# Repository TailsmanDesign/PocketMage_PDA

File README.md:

# PocketMage PDA
PocketMage is available on Crowd Supply! Check it out [here](https://pocketmage.org/back)!

@Ashtf 2025

## [Project Summary]

  This project is a PDA powered by an ESP32-S3 running a custom OS written in C++ using PlatformIO. This project utilizes an E-Ink and OLED screen in tandem to mitigate the refresh rate restrictions of an E-Ink panel while retaining the aesthetics and benefits of using E-Ink. This project is a work in progress and currently amounts to a simple GUI for navigating between apps, a text (.txt) file editor, and a basic file manager. More applications are planned for the future and a list of TO-DOs can be found below.

  At this point, the plan for this project is to get the software and hardware to maturity and once a finished product is achieved, a few things will happen. First, the project files (Code, KiCad schematics, 3D files) will be open-sourced and free for anyone to access. Next, I will likely begin selling kits that allow people to purchase all the parts required to build a device for themselves if they don't want to source the parts themselves. Finally, the community will be encouraged to help develop the software for the device and hopefully push it even further than I could myself.

  I will try my best to keep this GitHub up to date with the development of the device.

## [Getting Started]

Start with the docs site:

- [PocketMage Docs](https://talismandesign.github.io/PocketMage_PDA/docs/)
- [Build Environments](https://talismandesign.github.io/PocketMage_PDA/docs/development/build-environments)
- [Command Manual](https://talismandesign.github.io/PocketMage_PDA/docs/command-manual)
- [FAQ](https://talismandesign.github.io/PocketMage_PDA/docs/faq)
- [Scripting](https://talismandesign.github.io/PocketMage_PDA/docs/scripting)
- [App API Reference](https://talismandesign.github.io/PocketMage_PDA/docs/reference/app-api)

To build or extend apps, start with [APP_TEMPLATE.cpp](./Code/PocketMageOS/src/APP_TEMPLATE.cpp) and the [App API Reference](https://talismandesign.github.io/PocketMage_PDA/docs/reference/app-api).
The app walkthrough video is still useful for a first pass:
[Developing For the PocketMage](https://www.youtube.com/watch?v=3Ytc-3-BbMM)

## [Hardware]

- ESP32-S3 WROOM1 with 16 MB flash and 8 MB RAM. WiFi and Bluetooth supported.
- 3.1" 320x240px 1-bit SPI E-Ink panel (GDEQ031T10) with integrated driver
- 256x32px 1-bit SPI OLED (SSD1326, ER-OLED018-1W) with integrated driver
- MicroSD card slot with support for up to 2 TB
- TCA8418 I2C keyboard matrix IC
- Piezo buzzer (simple tones)
- Power button
- 1200 mAh pouch-style LiPo battery with JST PH (2 mm) connector
- USB Type-C connector
- PCF8563T I2C RTC module
- Expansion port with the following breakouts:
  - +3.3V
  - GND
  - I2C SDA
  - I2C SCL
  - SPI MOSI
  - SPI SCK
  - SPI MISO
  - GPIO A
  - GPIO B
  - GPIO C
  - GPIO D / UART TX (changeable with a solder jumper, default TX)
  - GPIO E / UART RX (changeable with a solder jumper, default RX)

## [Software]

- Text editor app (TXT)
- FileWiz file-management app
- Calendar app
- USB file transfer app
- COMM mesh chat app
- Settings app
- Tasks app
- Journal app
- Dictionary app (Lexicon)
- App loader for OTA apps
- Terminal app (Wrench scripting)
- SSH
- Commands supported through the home menu:
  - `roll dN` (dice roll, N = number of sides)
  - set time and date
  - directly open files in TXT or FileWiz by typing the name
  - and more

## [Planned Features]

- Timers and alarms
- E-book reader
- WiFi notes/calendar sync (Google Docs/Calendar)
- LoRa/Meshtastic add-on module
- Battery expansion add-on module
- Custom abbreviations
- Bluetooth keyboard support

## License

All files are distributed under the Apache-2.0 license:

PocketMage PDA - A clamshell note-taking and productivity device using E-Ink and OLED.

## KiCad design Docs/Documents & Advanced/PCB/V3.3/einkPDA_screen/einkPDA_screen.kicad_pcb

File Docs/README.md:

# PocketMage Documentation

The documentation site for the PocketMage PDA project.

**Live docs: <https://talismandesign.github.io/PocketMage_PDA/docs/>**

---

## What's in here

The `docs/` folder contains all the source Markdown files that make up the documentation site. Sections include:

- **Getting Started** - what PocketMage is, setup, and first steps
- **PocketMageOS** - the operating system and runtime model
- **Guides** - making apps, native apps, OTA apps, and scripting
- **Reference** - app API, system state, and the PocketMage library
- **Commands** - keymaps and built-in command reference
- **Features** - what PocketMage can do today
- **FAQ** - common questions about the device, building, flashing, and troubleshooting
- **Tutorials** - SD card formatting and setup walkthroughs

The site is built using [docmd](https://github.com/mgks/docmd) and configured via `docmd.config.js`.

---

## Local development

You'll need Node.js 18+ installed.

Install dependencies:

```
npm install
```

Start the local dev server with live reload:

```
npm run dev
```

Build the static site to the `site/` output folder:

```
npm run build
```

Preview the built site locally:

```
npm run preview
```

---

## Contributing to the docs

Documentation source files live in `docs/` as standard Markdown with YAML front matter for title and description metadata.

To add or edit a page:

1. Create or modify a `.md` file in the appropriate subfolder under `docs/`.
2. If you are adding a new page, add it to the `navigation` array in `docmd.config.js` so it appears in the sidebar.
3. Run `npm run dev` to preview your changes locally before submitting.

Keep the writing short and direct. Use the overview pages to route readers into the exact guide or reference page they need.

---

## Project links

- Main repo: <https://github.com/TalismanDesign/PocketMage_PDA>
- Discord: <https://discord.gg/KSCapSf4XH>
- Website: <https://pocketmage.org/>

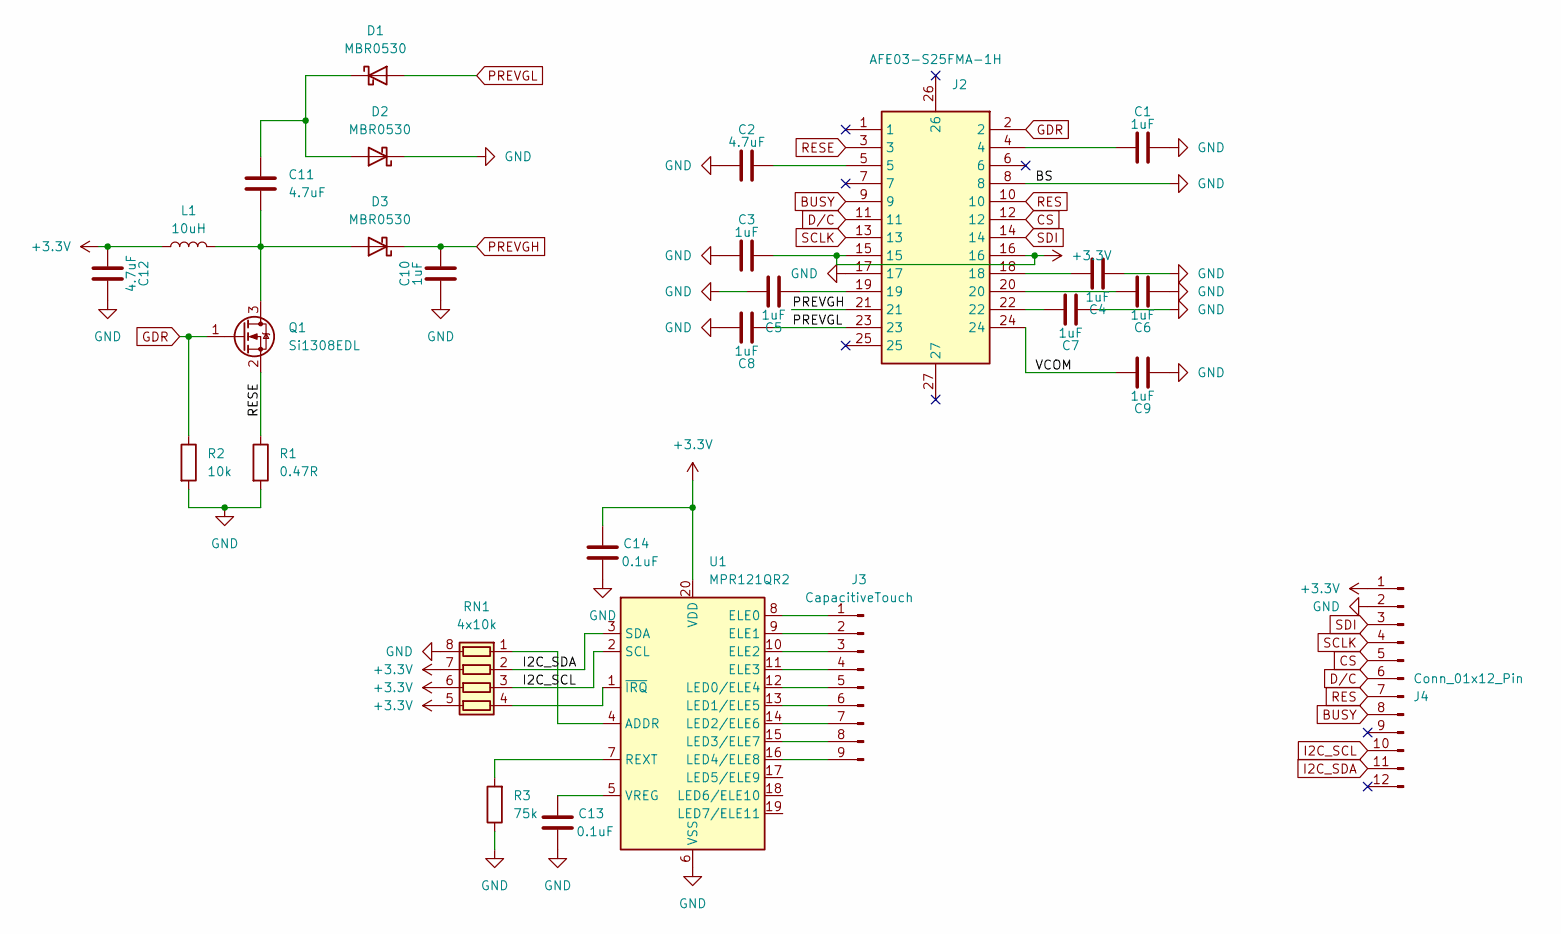
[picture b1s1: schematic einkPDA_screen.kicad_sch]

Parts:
C1, C3, C4, C5, C6, C7, C8, C9, C10: 1uF; C_0402_1005Metric; MPN C52923
C2, C12: 4.7uF; C_0402_1005Metric; MPN C23733
C11: 4.7uF; C_0805_2012Metric; MPN C1779
C13, C14: 0.1uF; C_0402_1005Metric; MPN C1525
D1, D2, D3: MBR0530; D_SOD-123; MPN C77336
J2: AFE03-S25FMA-1H; MPN C262544
J3: CapacitiveTouch; TouchSlider-9_50x10mm
J4: Conn_01x12_Pin; AFC01-S12FCA-00; MPN C262661
L1: 10uH; L_Cenker_CKCS5020; MPN C52281
Q1: Si1308EDL; SOT-323_SC-70; MPN C7603347
R1: 0.47R; R_0603_1608Metric; MPN C3013349
R2: 10k; R_0805_2012Metric; MPN C17414
R3: 75k; R_0603_1608Metric; MPN C23242
RN1: 4x10k; R_Array_Concave_4x0603; MPN C29718
U1: MPR121QR2; UQFN-20_3x3mm_P0.4mm; MPN C91322

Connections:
+3.3V: C3.2, C12.1, C14.1, J2.15, J2.16, J4.1, L1.1, RN1.5 (R4.2), RN1.6 (R3.2), RN1.7 (R2.2), U1.20 (VDD)
/VCOM: C9.2, J2.24
BUSY: J2.9, J4.8
CS: J2.12, J4.5
D/C: J2.11, J4.6
GDR: J2.2, Q1.1 (G), R2.1
GND: C1.2, C2.1, C3.1, C4.1, C5.2, C6.1, C7.1, C8.2, C9.1, C10.1, C12.2, C13.2, C14.2, D2.1 (K), J2.8, J2.17, J4.2, R1.2, R2.2, R3.1, RN1.8 (R1.2), U1.6 (VSS)
I2C_SCL: J4.10, RN1.3 (R3.1), U1.2 (SCL)
I2C_SDA: J4.11, RN1.2 (R2.1), U1.3 (SDA)
unnamed: C1.1, J2.4
unnamed: C2.2, J2.5
unnamed: C4.2, J2.18
unnamed: C5.1, J2.19
unnamed: C6.2, J2.20
unnamed: C7.2, J2.22
unnamed: C11.1, D1.1 (K), D2.2 (A)
unnamed: C11.2, D3.2 (A), L1.2, Q1.3 (D)
unnamed: J3.1, U1.8 (ELE0)
unnamed: J3.2, U1.9 (ELE1)
unnamed: J3.3, U1.10 (ELE2)
unnamed: J3.4, U1.11 (ELE3)
unnamed: J3.5, U1.12 (LED0/ELE4)
unnamed: J3.6, U1.13 (LED1/ELE5)
unnamed: J3.7, U1.14 (LED2/ELE6)
unnamed: J3.8, U1.15 (LED3/ELE7)
unnamed: J3.9, U1.16 (LED4/ELE8)
unnamed: RN1.1 (R1.1), U1.4 (ADDR)
unnamed: RN1.4 (R4.1), U1.1 (~IRQ)
unnamed: R3.2, U1.7 (REXT)
unnamed: C13.1, U1.5 (VREG)
PREVGH: C10.2, D3.1 (K), J2.21
PREVGL: C8.1, D1.2 (A), J2.23
RES: J2.10, J4.7
RESE: J2.3, Q1.2 (S), R1.1
SCLK: J2.13, J4.4
SDI: J2.14, J4.3

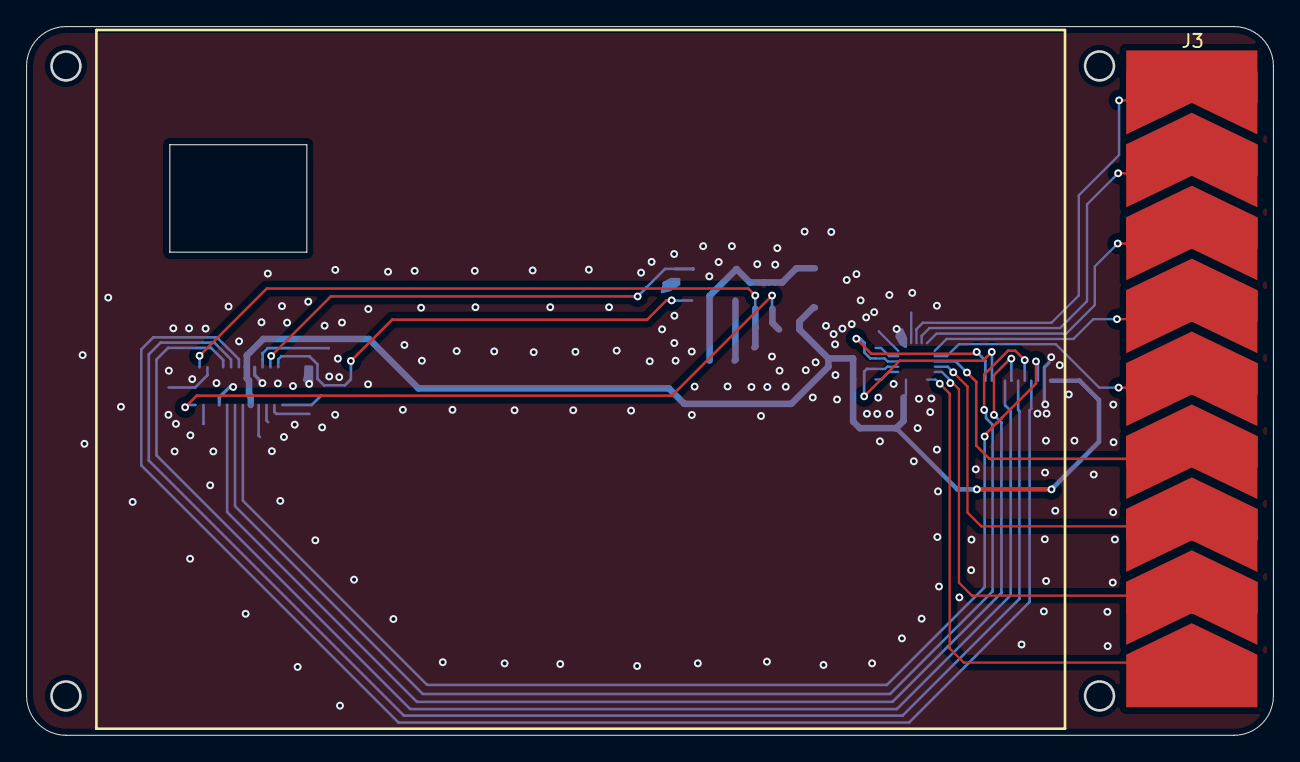
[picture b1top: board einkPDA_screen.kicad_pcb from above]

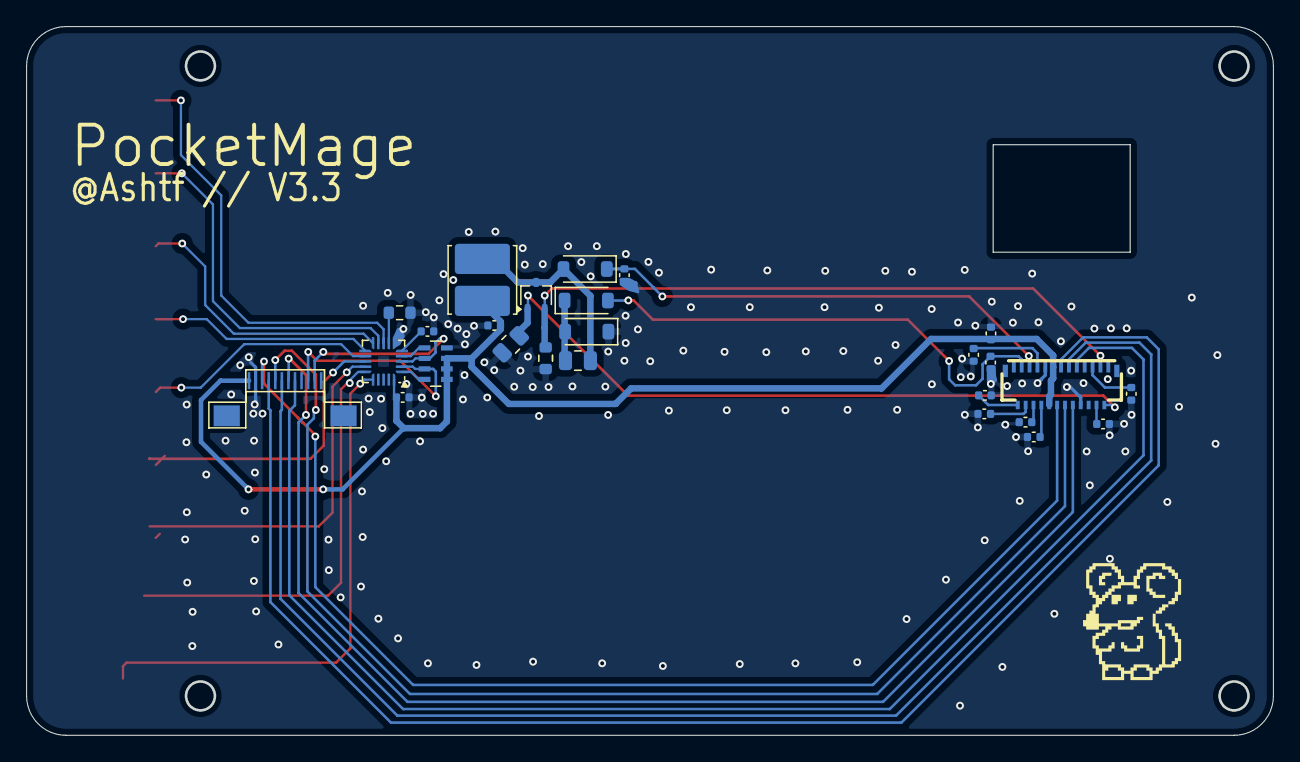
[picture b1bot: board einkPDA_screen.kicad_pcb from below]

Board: 2 copper layers, 95.0 x 54.0 mm, 27 parts (26 on the bottom side), 36 nets.

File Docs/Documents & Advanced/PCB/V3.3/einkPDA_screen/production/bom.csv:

Designator,Footprint,Quantity,Value,LCSC Part #
"C1, C10, C3, C4, C5, C6, C7, C8, C9",0402,9,1uF,C52923
C11,0805,1,4.7uF,C1779
"C12, C2",0402,2,4.7uF,C23733
"C13, C14",0402,2,0.1uF,C1525
"D1, D2, D3",D_SOD-123,3,MBR0530,C77336
J2,AFE03-S25FMA-1H,1,~,C262544
J3,TouchSlider-9_50x10mm,1,CapacitiveTouch,
J4,AFC01-S12FCA-00,1,Conn_01x12_Pin,C262661
L1,L_Cenker_CKCS5020,1,10uH,C52281
Q1,SOT-323_SC-70,1,Si1308EDL,C7603347
R1,0603,1,0.47R,C3013349
R2,0805,1,10k,C17414
R3,0603,1,75k,C23242
RN1,R_Array_Concave_4x0603,1,4x10k,C29718
U1,UQFN-20_3x3mm_P0.4mm,1,MPR121QR2,C91322

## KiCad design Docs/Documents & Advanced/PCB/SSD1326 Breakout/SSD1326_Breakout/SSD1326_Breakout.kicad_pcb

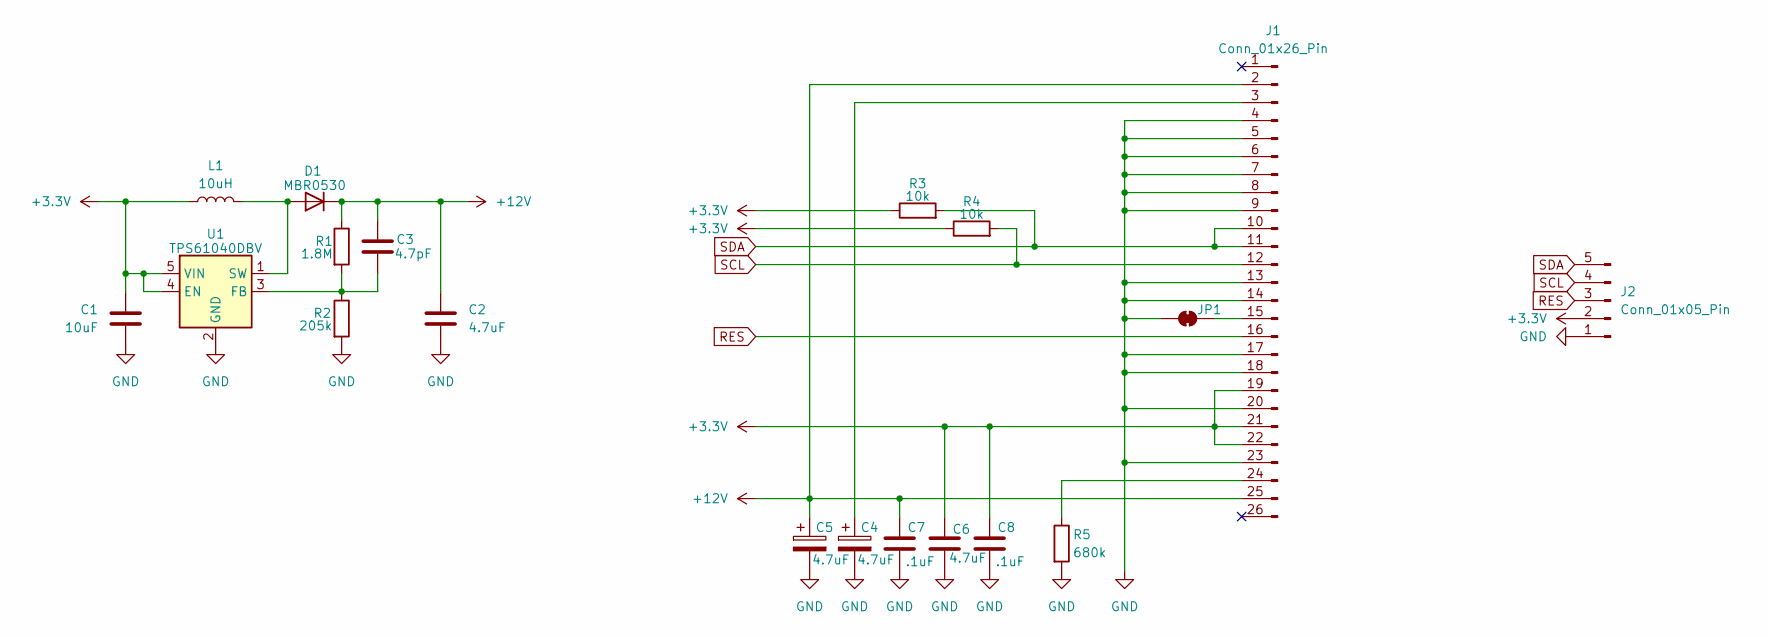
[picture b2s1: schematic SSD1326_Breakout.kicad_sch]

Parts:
C1: 10uF; C_0805_2012Metric; LCSC PART # C15850
C2, C6: 4.7uF; C_1206_3216Metric; LCSC PART # C29823
C3: 4.7pF; C_0603_1608Metric; LCSC PART # C1669
C4, C5: 4.7uF; CP_EIA-3216-18_Kemet-A; LCSC PART # C7189
C7, C8: .1uF; C_0805_2012Metric; LCSC PART # C28233
D1: MBR0530; D_SOD-123; LCSC PART # C77336
J1: Conn_01x26_Pin; FPC-SMD_AFC24-S26FIA [DUAL-SIDE]; LCSC PART # C262684
J2: Conn_01x05_Pin; PinHeader_1x05_P2.54mm_Vertical
JP1: SolderJumper_2_Bridged; SolderJumper-2_P1.3mm_Bridged_RoundedPad1.0x1.5mm
L1: 10uH; L_Chilisin_BMRx00060630; LCSC PART # C5189958
R1: 1.8M; R_0805_2012Metric; LCSC PART # C17399
R2: 205k; R_0805_2012Metric; LCSC PART # C218417
R3, R4: 10k; R_0805_2012Metric; LCSC PART # C17414
R5: 680k; R_0805_2012Metric; LCSC PART # C17797
U1: TPS61040DBV; SOT-23-5; LCSC PART # C7722

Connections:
+3.3V: C1.2, C6.1, C8.1, J1.19, J1.21, J1.22, J2.2, L1.1, R3.1, R4.1, U1.4 (EN), U1.5 (VIN)
+12V: C2.1, C3.2, C5.1, C7.1, D1.1 (K), J1.2, J1.25, R1.1
GND: C1.1, C2.2, C4.2, C5.2, C6.2, C7.2, C8.2, J1.4, J1.5, J1.6, J1.7, J1.8, J1.9, J1.13, J1.14, J1.17, J1.18, J1.20, J1.23, J2.1, JP1.1 (A), R2.2, R5.2, U1.2 (GND)
unnamed: D1.2 (A), L1.2, U1.1 (SW)
unnamed: C4.1, J1.3
unnamed: J1.15, JP1.2 (B)
unnamed: J1.24, R5.1
unnamed: C3.1, R1.2, R2.1, U1.3 (FB)
RES: J1.16, J2.3
SCL: J1.12, J2.4, R4.2
SDA: J1.10, J1.11, J2.5, R3.2

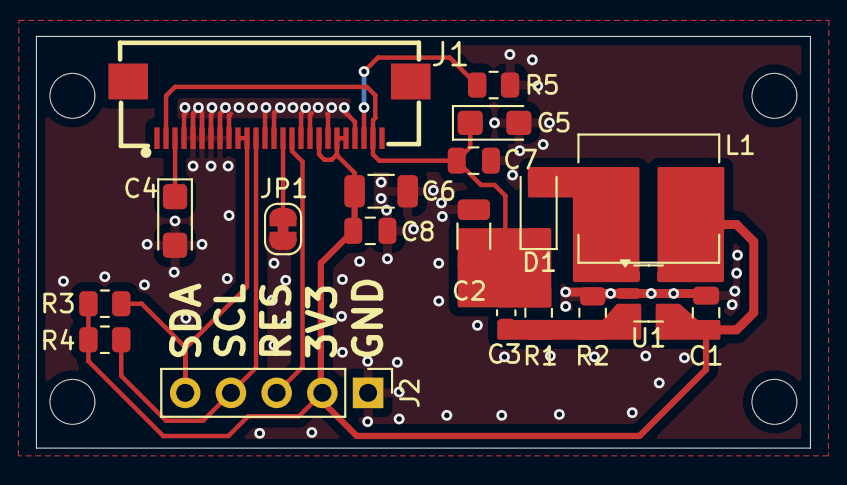
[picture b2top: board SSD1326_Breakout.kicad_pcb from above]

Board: 2 copper layers, 43.0 x 22.9 mm, 19 parts (0 on the bottom side), 11 nets.

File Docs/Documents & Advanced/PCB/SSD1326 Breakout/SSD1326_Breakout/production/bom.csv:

Designator,Footprint,Quantity,Value,LCSC Part #
C1,0805,1,10uF,
"C2, C6",1206,2,4.7uF,
C3,0603,1,4.7pF,
"C4, C5",CP_EIA-3216-18_Kemet-A,2,4.7uF,
"C7, C8",0805,2,.1uF,
D1,D_SOD-123,1,MBR0530,
J1,FPC-SMD_AFC24-S26FIA [DUAL-SIDE],1,Conn_01x26_Pin,
J2,PinHeader_1x05_P2.54mm_Vertical,1,Conn_01x05_Pin,
L1,L_Chilisin_BMRx00060630,1,10uH,
R1,0805,1,1.8M,
R2,0805,1,205k,
"R3, R4",0805,2,10k,
R5,0805,1,680k,
U1,SOT-23-5,1,TPS61040DBV,

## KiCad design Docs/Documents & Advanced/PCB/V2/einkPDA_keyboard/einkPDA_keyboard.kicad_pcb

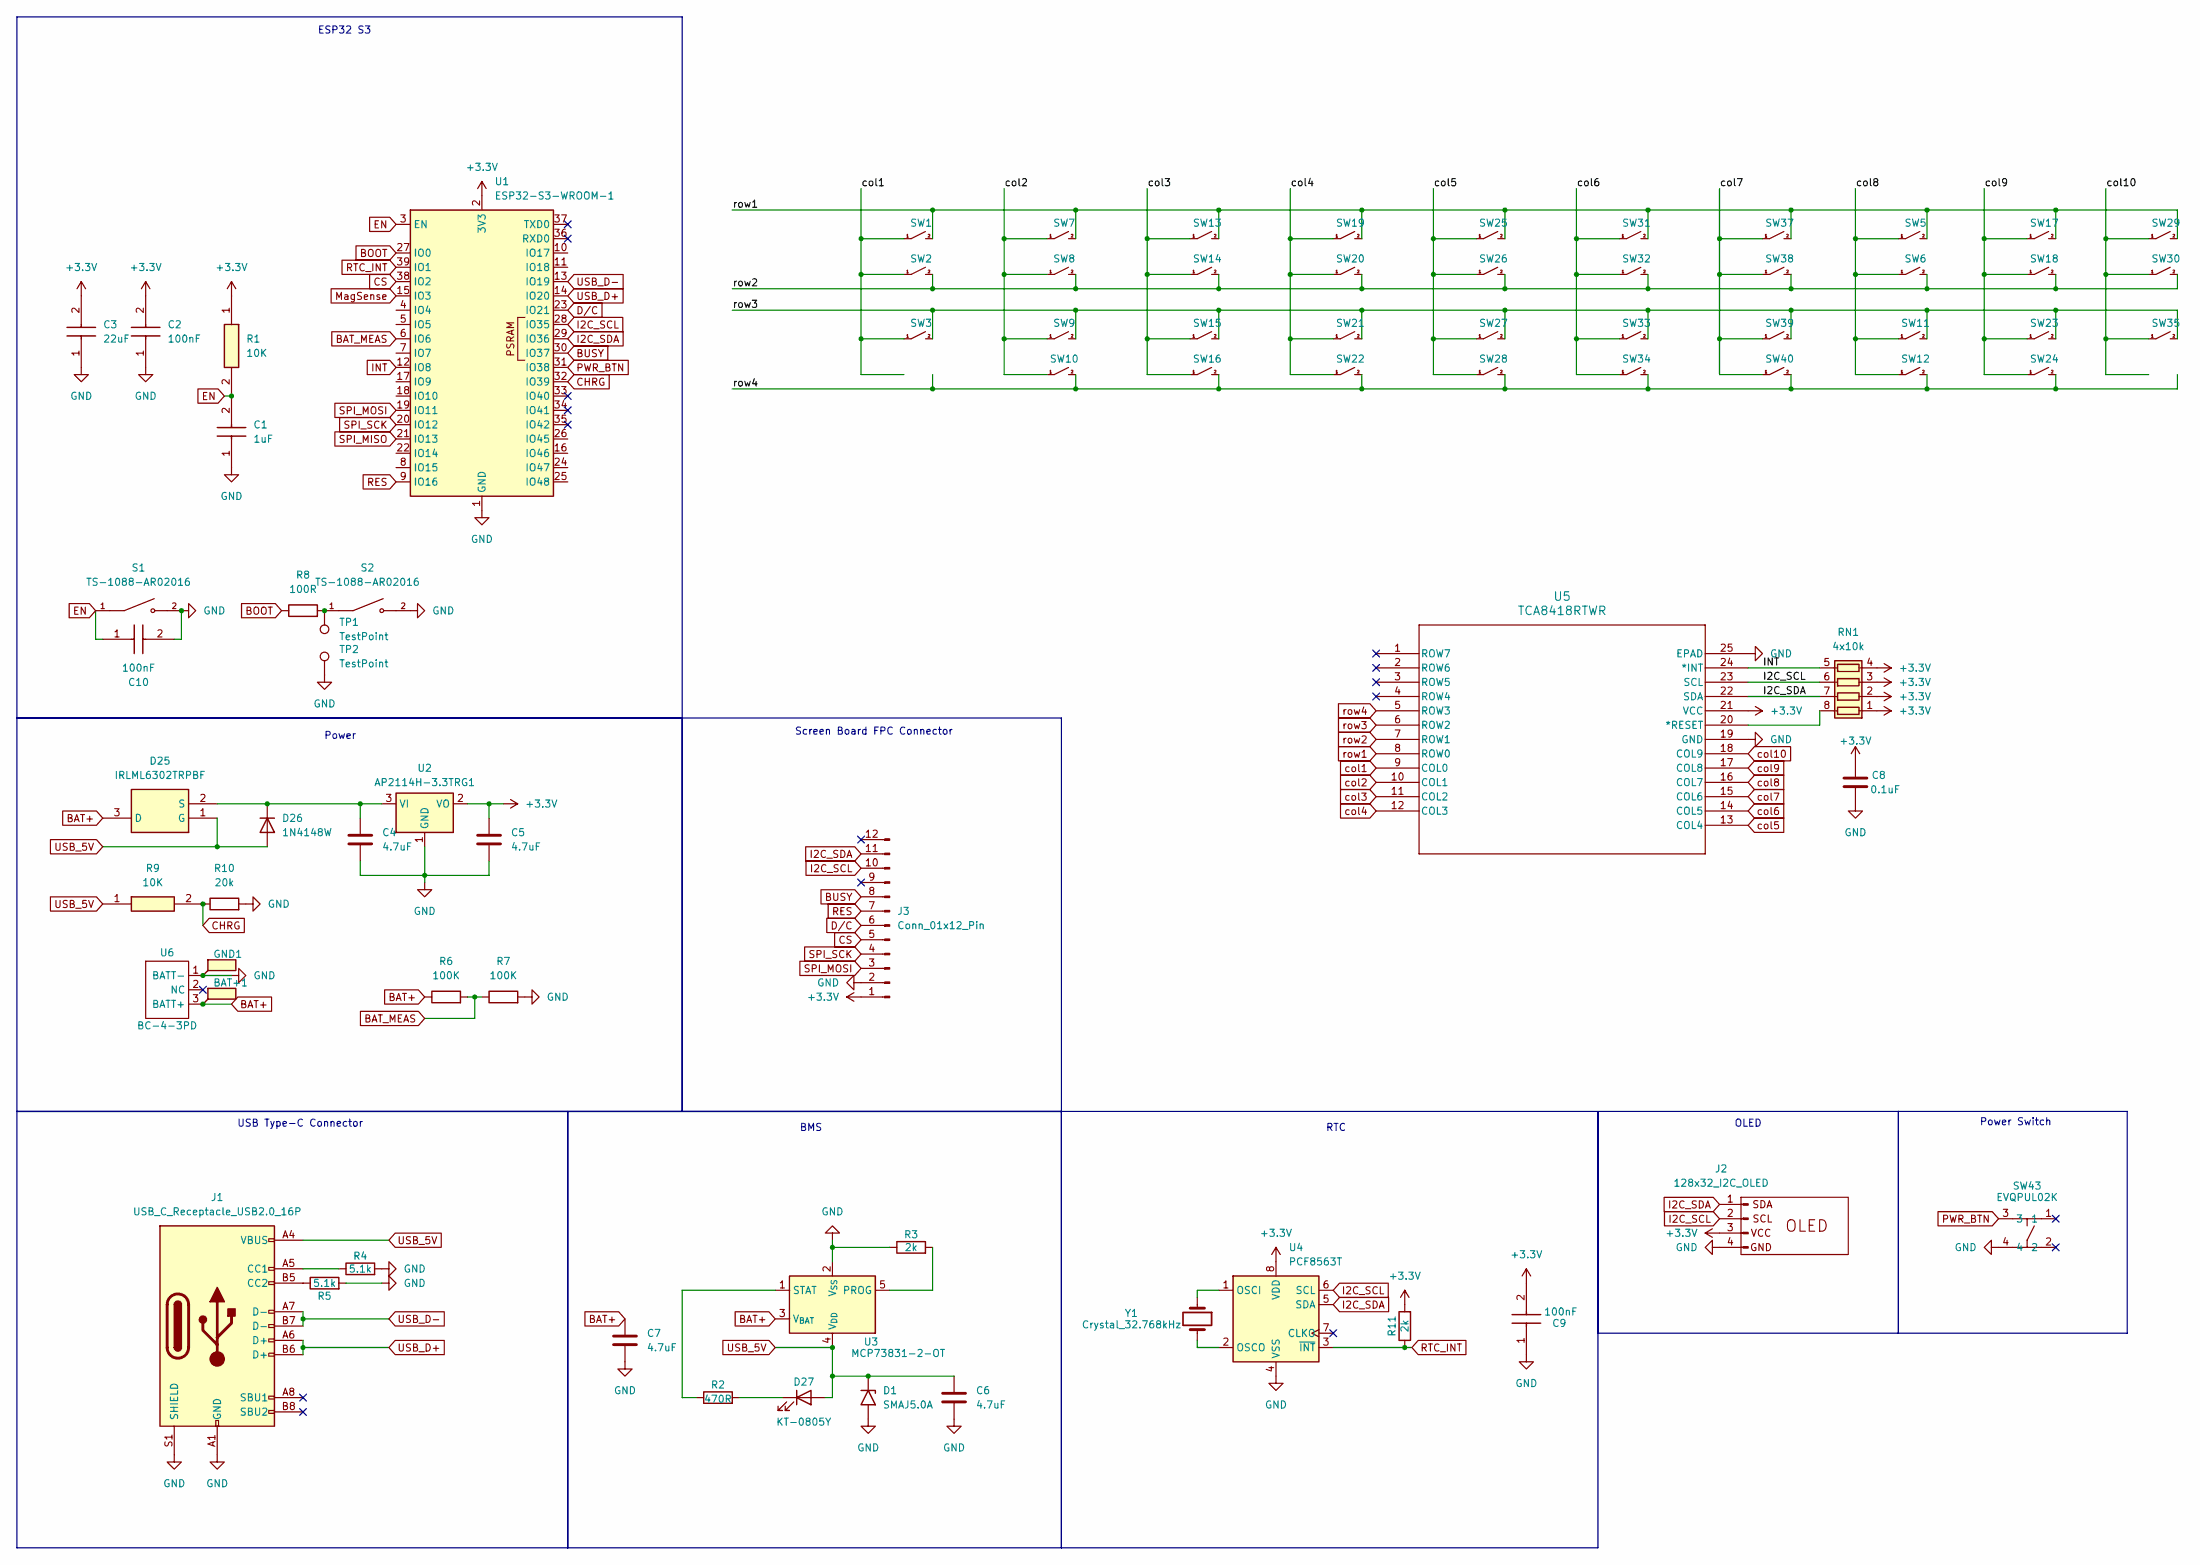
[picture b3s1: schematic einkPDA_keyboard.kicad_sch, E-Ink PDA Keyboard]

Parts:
BAT+1: TestPoint_Flag; TestPoint_Pad_D1.5mm
C1: 1uF; CAPC2012X135N; Mouser Part Number 187-CL21B105KBFNNNE
C2, C9, C10: 100nF; CAPC2012X95N; Mouser Part Number 603-CC805KRX7R9BB104
C3: 22uF; CAPC2012X140N; Mouser Part Number 187-CL21A226MAQNNNE
C4, C5, C6, C7: 4.7uF; C_0805_2012Metric; LCSC Part # CL21A475KAQNNNE
C8: 0.1uF; C_0402_1005Metric; LCSC Part # CL05B104KO5NNNC
D1: SMAJ5.0A; D_SMA
D25: IRLML6302TRPBF; SOT95P237X112-3N; Mouser Part Number 942-IRLML6302TRPBF
D26: 1N4148W; D_SOD-123; LCSC Part # 1N4148W
D27: KT-0805Y; LED_0805_2012Metric; LCSC Part # KT-0805Y
GND1: TestPoint_Flag; TestPoint_Pad_D1.5mm
J1: USB_C_Receptacle_USB2.0_16P; USB_C_Receptacle_G-Switch_GT-USB-7010ASV; LCSC Part # GT-USB-7010ASV
J2: 128x32_I2C_OLED; 128x32 I2C OLED
J3: Conn_01x12_Pin; AFC01-S12FCA-00; LCSC Part # AFC01-S12FCA-00:AFC01-S12FCA-00
R1, R9: 10K; R_0805_2012Metric; Mouser Part Number 303-0805W8F1002T5E
R2: 470R; R_0805_2012Metric; LCSC Part # 0805W8F4700T5E
R3, R11: 2k; R_0805_2012Metric; LCSC Part # 0805W8F2001T5E
R4, R5: 5.1k; R_0603_1608Metric; LCSC Part # 0603WAF5101T5E
R6, R7: 100K; R_1812_4532Metric; LCSC Part # FRC1812F1003TS
R8: 100R; R_1206_3216Metric; LCSC Part # 1206W4F1000T5E
R10: 20k; R_0603_1608Metric; LCSC Part # 0603WAF2002T5E
RN1: 4x10k; R_Array_Concave_4x0603; LCSC Part # 4D03WGJ0103T5E
S1, S2: TS-1088-AR02016; SW_TS-1088-AR02016; PARTREV N/A; LCSC Part # TS-1088-AR02016
SW1, SW2, SW3, SW5, SW6, SW7, SW8, SW9, SW10, SW11, SW12, SW13, SW14, SW15, SW16, SW17, SW18, SW19, SW20, SW21, SW22, SW23, SW24, SW25, SW26, SW27, SW28, SW29, SW30, SW31, SW32, SW33, SW34, SW35, SW37, SW38, SW39, SW40: contact_pad_SINGLE
SW43: EVQPUL02K; LCSC Part # EVQPUL02K
TP1, TP2: TestPoint; TestPoint_Pad_3.0x3.0mm
U1: ESP32-S3-WROOM-1; LCSC Part # ESP32-S3-WROOM-1
U2: AP2114H-3.3TRG1; SOT-223-3_TabPin2; LCSC Part # AP2114H-3.3TRG1
U3: MCP73831-2-OT; SOT-23-5; LCSC Part # MCP73831-2-OT
U4: PCF8563T; SOIC-8_3.9x4.9mm_P1.27mm
U5: TCA8418RTWR; RTW24_2P45X2P45; LCSC Part # TCA8418RTWR
U6: BC-4-3PD; LCSC Part # BC-4-3PD
Y1: Crystal_32.768kHz; Crystal_SMD_3215-2Pin_3.2x1.5mm; LCSC Part # XKXGI-SUA-32.768K

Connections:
+3.3V: C2.2, C3.2, C5.1, C8.1, C9.2, J2.3 (VCC), J3.1, R1.1, R11.2, RN1.1 (R1.1), RN1.2 (R2.1), RN1.3 (R3.1), RN1.4 (R4.1), U1.2 (3V3), U2.2 (VO), U4.8 (VDD), U5.21 (VCC)
BAT+: BAT+1.1, C7.1, D25.3 (D), R6.1, U3.3 (V_{BAT}), U6.3 (BATT+)
BAT_MEAS: R6.2, R7.1, U1.6 (IO6)
BOOT: R8.1, U1.27 (IO0)
BUSY: J3.8, U1.30 (IO37)
CHRG: R9.2, R10.1, U1.32 (IO39)
CS: J3.5, U1.38 (IO2)
D/C: J3.6, U1.23 (IO21)
EN: C1.2, C10.1, R1.2, S1.1, U1.3 (EN)
GND: C1.1, C2.1, C3.1, C4.2, C5.2, C6.2, C7.2, C8.2, C9.1, C10.2, D1.2 (A2), GND1.1, J1.A1 (GND), J1.A12 (GND), J1.B1 (GND), J1.B12 (GND), J1.S1 (SHIELD), J2.4 (GND), J3.2, R3.1, R4.2, R5.2, R7.2, R10.2, S1.2, S2.2, SW43.4, TP2.1, U1.1 (GND), U1.40 (GND), U1.41 (GND), U2.1 (GND), U3.2 (V_{SS}), U4.4 (VSS), U5.19 (GND), U5.25 (EPAD), U5.V, U6.1 (BATT-)
I2C_SCL: J2.2 (SCL), J3.10, RN1.6 (R3.2), U1.28 (IO35), U4.6 (SCL), U5.23 (SCL)
I2C_SDA: J2.1 (SDA), J3.11, RN1.7 (R2.2), U1.29 (IO36), U4.5 (SDA), U5.22 (SDA)
INT: RN1.5 (R4.2), U1.12 (IO8), U5.24 (*INT)
MagSense: U1.15 (IO3)
unnamed: C4.1, D25.2 (S), D26.1 (K), U2.3 (VI)
unnamed: D27.1 (K), R2.2
unnamed: J1.A5 (CC1), R4.1
unnamed: J1.B5 (CC2), R5.1
unnamed: R8.2, S2.1, TP1.1
unnamed: RN1.8 (R1.2), U5.20 (*RESET)
unnamed: R3.2, U3.5 (PROG)
unnamed: R2.1, U3.1 (STAT)
unnamed: U4.1 (OSCI), Y1.1
unnamed: U4.2 (OSCO), Y1.2
PWR_BTN: SW43.3, U1.31 (IO38)
RES: J3.7, U1.9 (IO16)
RTC_INT: R11.1, U1.39 (IO1), U4.3 (~INT)
SPI_MISO: U1.21 (IO13)
SPI_MOSI: J3.3, U1.19 (IO11)
SPI_SCK: J3.4, U1.20 (IO12)
USB_5V: C6.1, D1.1 (A1), D25.1 (G), D26.2 (A), D27.2 (A), J1.A4 (VBUS), J1.A9 (VBUS), J1.B4 (VBUS), J1.B9 (VBUS), R9.1, U3.4 (V_{DD})
USB_D+: J1.A6 (D+), J1.B6 (D+), U1.14 (IO20)
USB_D-: J1.A7 (D-), J1.B7 (D-), U1.13 (IO19)
col1: SW1.1, SW2.1, SW3.1, U5.9 (COL0)
col2: SW7.1, SW8.1, SW9.1, SW10.1, U5.10 (COL1)
col3: SW13.1, SW14.1, SW15.1, SW16.1, U5.11 (COL2)
col4: SW19.1, SW20.1, SW21.1, SW22.1, U5.12 (COL3)
col5: SW25.1, SW26.1, SW27.1, SW28.1, U5.13 (COL4)
col6: SW31.1, SW32.1, SW33.1, SW34.1, U5.14 (COL5)
col7: SW37.1, SW38.1, SW39.1, SW40.1, U5.15 (COL6)
col8: SW5.1, SW6.1, SW11.1, SW12.1, U5.16 (COL7)
col9: SW17.1, SW18.1, SW23.1, SW24.1, U5.17 (COL8)
col10: SW29.1, SW30.1, SW35.1, U5.18 (COL9)
row1: SW1.2, SW5.2, SW7.2, SW13.2, SW17.2, SW19.2, SW25.2, SW29.2, SW31.2, SW37.2, U5.8 (ROW0)
row2: SW2.2, SW6.2, SW8.2, SW14.2, SW18.2, SW20.2, SW26.2, SW30.2, SW32.2, SW38.2, U5.7 (ROW1)
row3: SW3.2, SW9.2, SW11.2, SW15.2, SW21.2, SW23.2, SW27.2, SW33.2, SW35.2, SW39.2, U5.6 (ROW2)
row4: SW10.2, SW12.2, SW16.2, SW22.2, SW24.2, SW28.2, SW34.2, SW40.2, U5.5 (ROW3)

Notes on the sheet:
ESP32 S3
RTC
Screen Board FPC Connector
Power
OLED
USB Type-C Connector
Power Switch
BMS

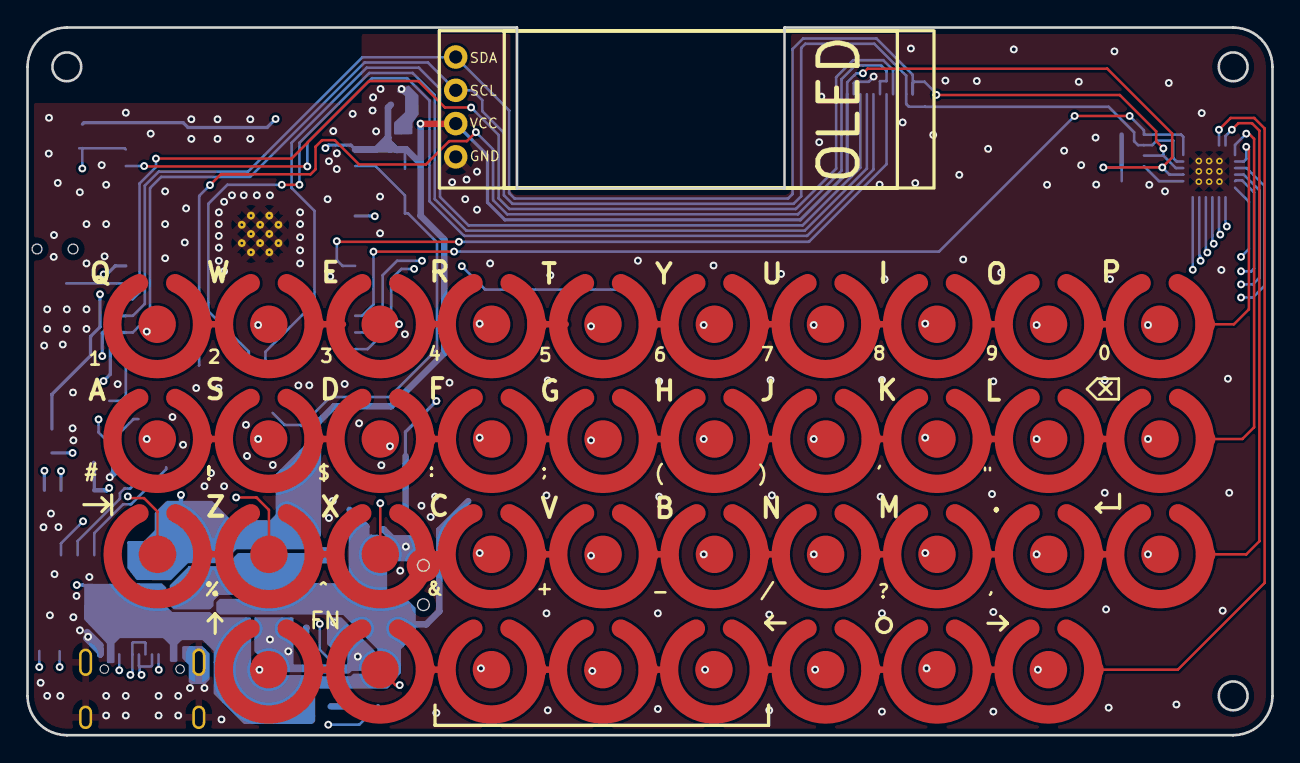
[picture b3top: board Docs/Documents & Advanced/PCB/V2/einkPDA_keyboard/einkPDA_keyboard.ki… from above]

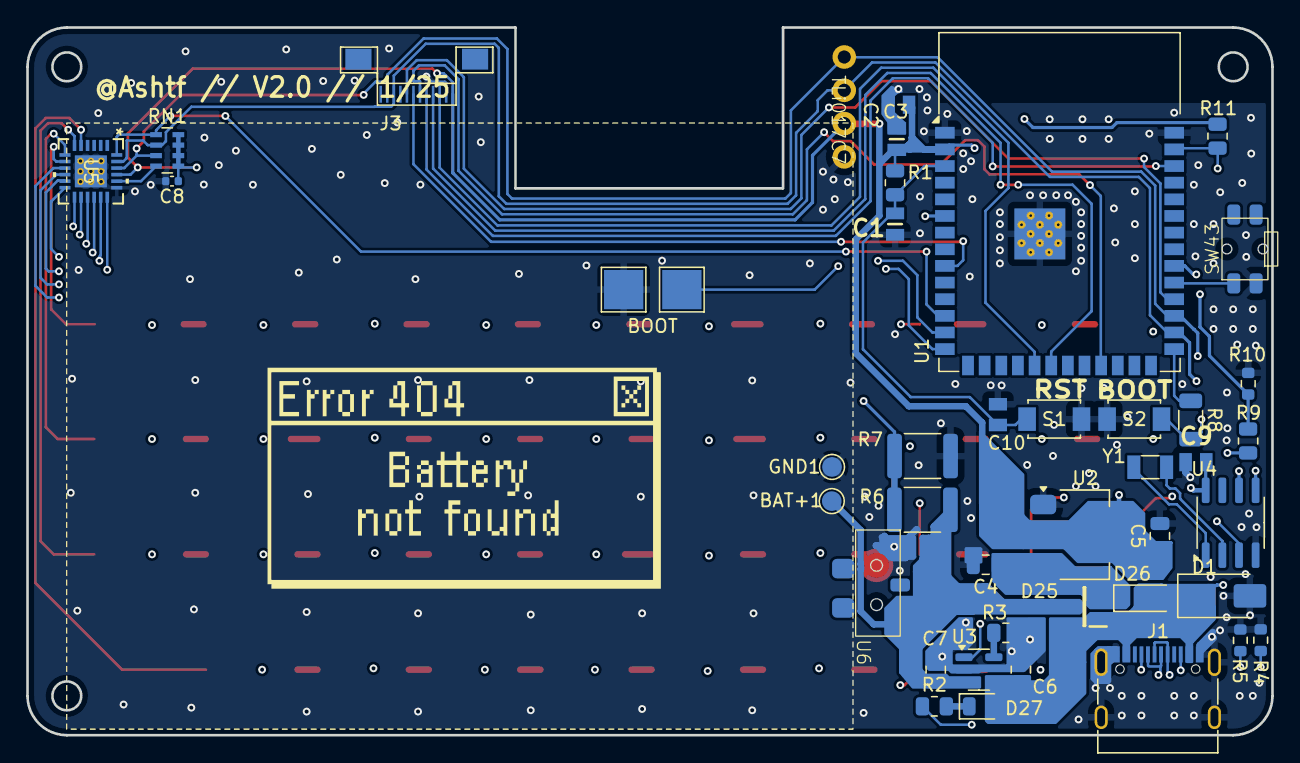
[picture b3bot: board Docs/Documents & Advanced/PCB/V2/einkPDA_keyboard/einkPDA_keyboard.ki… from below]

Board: 4 copper layers, 95.0 x 54.0 mm, 81 parts (42 on the bottom side), 45 nets.

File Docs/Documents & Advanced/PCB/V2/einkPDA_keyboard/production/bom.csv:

Designator,Footprint,Quantity,Value,LCSC Part #
"BAT+1, GND1",TestPoint_Pad_D1.5mm,2,TestPoint_Flag,
C1,CAPC2012X135N,1,1uF,CL21B105KBFNNNE
"C10, C2, C9",CAPC2012X95N,3,100nF,CC0805KRX7R9BB104
C3,CAPC2012X140N,1,22uF,CL21A226MAQNNNE
"C4, C5, C6, C7",0805,4,4.7uF,CL21A475KAQNNNE
C8,0402,1,0.1uF,CL05B104KO5NNNC
D1,D_SMA,1,SMAJ5.0A,
D25,SOT95P237X112-3N,1,IRLML6302TRPBF,IRLML6302TRPBF
D26,D_SOD-123,1,1N4148W,1N4148W
D27,0805,1,KT-0805Y,KT-0805Y
J1,USB_C_Receptacle_G-Switch_GT-USB-7010ASV,1,USB_C_Receptacle_USB2.0_16P,GT-USB-7010ASV
J2,128x32 I2C OLED,1,128x32_I2C_OLED,
J3,AFC01-S12FCA-00,1,Conn_01x12_Pin,AFC01-S12FCA-00:AFC01-S12FCA-00
"R1, R9",0805,2,10K,0805W8F1002T5E
R10,0603,1,20k,0603WAF2002T5E
"R11, R3",0805,2,2k,0805W8F2001T5E
R2,0805,1,470R,0805W8F4700T5E
"R4, R5",0603,2,5.1k,0603WAF5101T5E
"R6, R7",1812,2,100K,FRC1812F1003TS
R8,1206,1,100R,1206W4F1000T5E
RN1,R_Array_Concave_4x0603,1,4x10k,4D03WGJ0103T5E
"S1, S2",SW_TS-1088-AR02016,2,TS-1088-AR02016,TS-1088-AR02016
"SW1, SW10, SW11, SW12, SW13, SW14, SW15, SW16, SW17, SW18, SW19, SW2, SW20, SW21, SW22, SW23, SW24, SW25, SW26, SW27, SW28, SW29, SW3, SW30, SW31, SW32, SW33, SW34, SW35, SW37, SW38, SW39, SW40, SW5, SW6, SW7, SW8, SW9",contact_pad_SINGLE,38,~,
SW43,EVQPUL02K,1,EVQPUL02K,EVQPUL02K
"TP1, TP2",TestPoint_Pad_3.0x3.0mm,2,TestPoint,
U1,ESP32-S3-WROOM-1,1,ESP32-S3-WROOM-1,ESP32-S3-WROOM-1
U2,SOT-223-3_TabPin2,1,AP2114H-3.3TRG1,AP2114H-3.3TRG1
U3,SOT-23-5,1,MCP73831-2-OT,MCP73831-2-OT
U4,SOIC-8_3.9x4.9mm_P1.27mm,1,PCF8563T,
U5,RTW24_2P45X2P45,1,TCA8418RTWR,TCA8418RTWR
U6,BC-4-3PD,1,BC-4-3PD,BC-4-3PD
Y1,Crystal_SMD_3215-2Pin_3.2x1.5mm,1,Crystal_32.768kHz,XKXGI-SUA-32.768K
